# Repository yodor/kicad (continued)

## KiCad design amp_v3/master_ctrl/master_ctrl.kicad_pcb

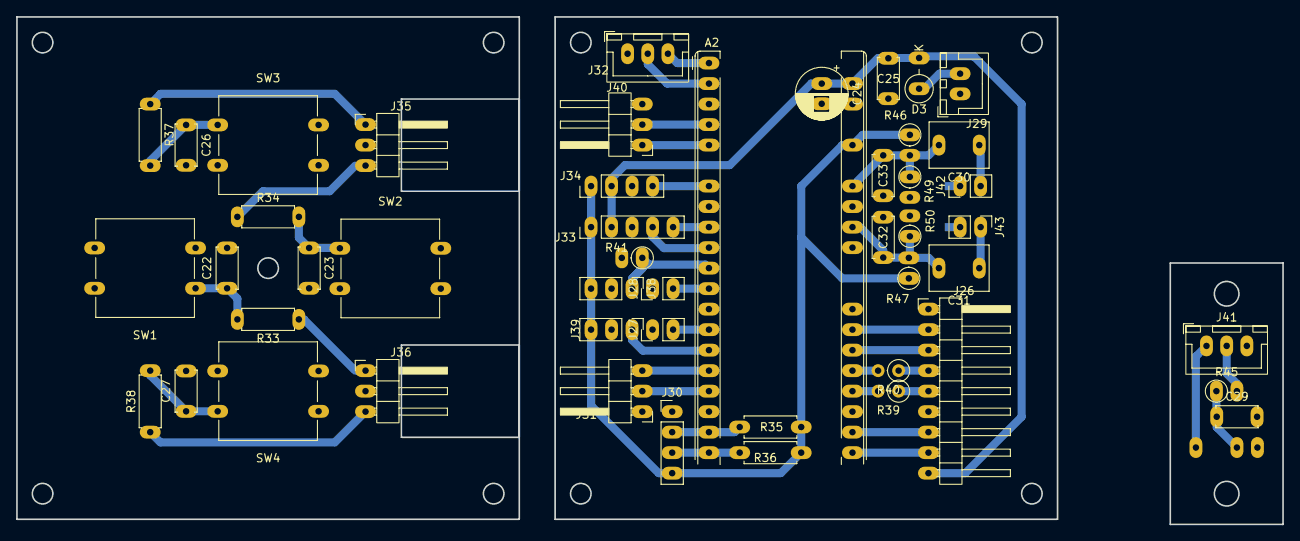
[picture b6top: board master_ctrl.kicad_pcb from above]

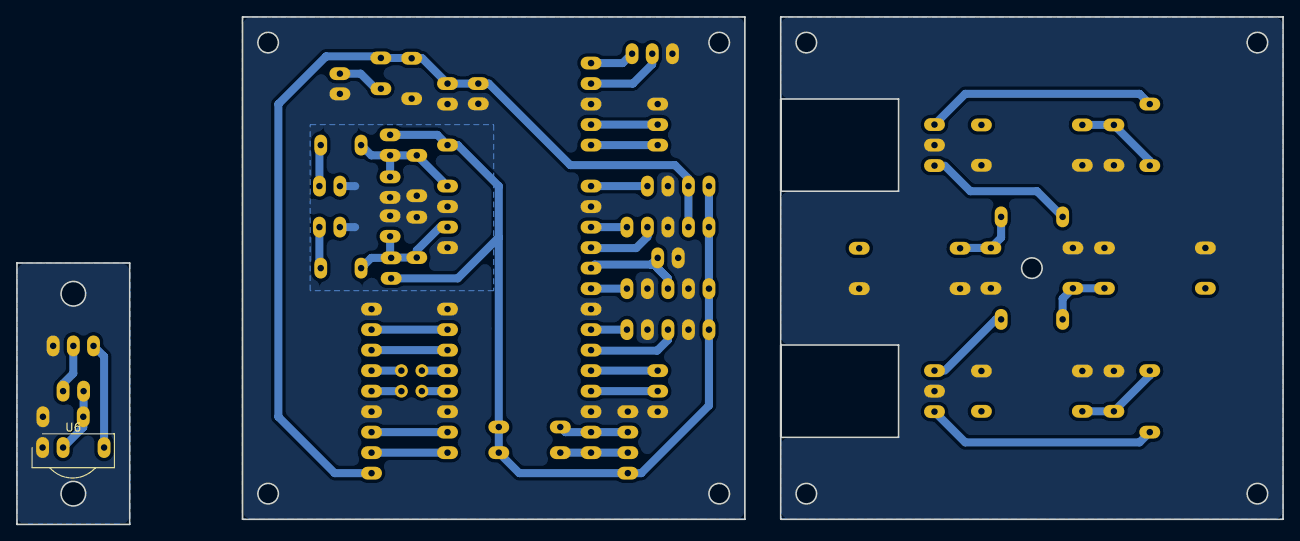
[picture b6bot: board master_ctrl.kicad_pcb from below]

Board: 2 copper layers, 156.8 x 62.9 mm, 51 parts (3 on the bottom side), 39 nets.

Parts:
A2: RaspberryPi_Pico_W; RaspberryPi_Pico_Common_THT
C22, C23, C25, C26, C27, C29: 100nF; C_Disc_D5.0mm_W2.5mm_P5.00mm
C24: 100uF low; CP_Radial_D6.3mm_P2.50mm
C30, C31: 1uF; C_Rect_L7.2mm_W5.5mm_P5.00mm_FKS2_FKP2_MKS2_MKP2
C32, C33: 10nF; C_Disc_D5.0mm_W2.5mm_P5.00mm
D3: 1n5819; D_DO-41_SOD81_P3.81mm_Vertical_CathodeUp
J26: TFT; PinHeader_1x09_P2.54mm_Horizontal
J27: PWR_CTRL; PinHeader_1x02_P2.54mm_Vertical
J28: PWR_BTN_LED; PinHeader_1x02_P2.54mm_Vertical
J29: PWR_IN; JST_XH_B2B-XH-A_1x02_P2.50mm_Vertical
J30: I2C; PinHeader_1x04_P2.54mm_Vertical
J31: BTN_VOL; PinHeader_1x03_P2.54mm_Horizontal
J32: BTN_MENU; PinHeader_1x03_P2.54mm_Horizontal
J33: ALPS; PinHeader_1x05_P2.54mm_Vertical
J34: PWR_RLY; PinHeader_1x04_P2.54mm_Vertical
J35: BTN_EXT1; PinHeader_1x03_P2.54mm_Horizontal
J36: BTN_EXT2; PinHeader_1x03_P2.54mm_Horizontal
J38: MUTE; PinHeader_1x03_P2.54mm_Vertical
J39: IR; PinHeader_1x03_P2.54mm_Vertical
J40: UART; JST_XH_B3B-XH-A_1x03_P2.50mm_Vertical
J41: IR_SENSOR; JST_XH_B3B-XH-A_1x03_P2.50mm_Vertical
J42: S_AIN_L; PinHeader_1x02_P2.54mm_Vertical
J43: S_AIN_R; PinHeader_1x02_P2.54mm_Vertical
NT3, NT4: NetTie_2; NetTie-2_SMD_Pad1.0o
R33, R34, R37, R38: 1k; R_Axial_DIN0207_L6.3mm_D2.5mm_P7.62mm_Horizontal
R35, R36: 4.7K; R_Axial_DIN0207_L6.3mm_D2.5mm_P7.62mm_Horizontal
R39, R40: 22; R_Axial_DIN0207_L6.3mm_D2.5mm_P2.54mm_Vertical
R41, R46, R47, R49, R50: 10K; R_Axial_DIN0207_L6.3mm_D2.5mm_P2.54mm_Vertical
R45: 100; R_Axial_DIN0207_L6.3mm_D2.5mm_P2.54mm_Vertical
SW1: SW_LT; SW_SPST_Omron_B3F-50xx
SW2: SW_RT; SW_SPST_Omron_B3F-50xx
SW3: SW_UP; SW_SPST_Omron_B3F-50xx
SW4: SW_DN; SW_SPST_Omron_B3F-50xx
U6: TSOP312xx; Vishay_CAST-3Pin

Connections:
/Main Board/3.3V_PICO: A2.36 (3V3), J30.4, J33.1, J34.1, J38.3, J39.3, J41.2, R35.1, R36.1, R45.2, R46.1, R47.1
/Main Board/5V_board1: D3.2 (A), J29.2
/Main Board/5v_local: A2.39 (VSYS), C24.1, C25.1, D3.1 (K), J26.9, J33.2, J34.2
/Main Board/ADC_L: A2.34 (GPIO28_ADC2), C30.2, C33.1, R46.2, R49.1
/Main Board/ADC_R: A2.32 (GPIO27_ADC1), C31.2, C32.2, R47.2, R50.1
/Main Board/AGND_L: J42.1, NT4.1
/Main Board/AGND_PICO: A2.31 (GPIO26_ADC0), A2.33 (AGND), C32.1, C33.2, NT3.2, NT4.2, R49.2, R50.2
/Main Board/AGND_R: J43.2, NT3.1
/Main Board/ALPS_L: A2.10 (GPIO7), J33.4
/Main Board/ALPS_R: A2.9 (GPIO6), J33.5
/Main Board/AUDIO_L: C30.1, J42.2
/Main Board/AUDIO_R: C31.1, J43.1
/Main Board/BTN_DN: A2.17 (GPIO13), J31.2, J36.3, R38.1
/Main Board/BTN_LT: A2.16 (GPIO12), J31.3, J36.1, R33.1
/Main Board/BTN_RT: A2.5 (GPIO3), J32.1, J35.3, R34.1
/Main Board/BTN_UP: A2.4 (GPIO2), J32.2, J35.1, R37.1
/Main Board/IR: A2.15 (GPIO11), J39.1, J41.1, U6.3 (OUT)
/Main Board/MUTE_CTRL: A2.11 (GPIO8), J38.1, R41.1
/Main Board/PWR_BTN_LED: A2.12 (GPIO9), J28.2
/Main Board/PWR_CTRL: A2.14 (GPIO10), J27.2
/Main Board/RLCTRL: A2.7 (GPIO5), J34.4
/Main Board/SCL: A2.20 (GPIO15), J30.3, R36.2
/Main Board/SDA: A2.19 (GPIO14), J30.2, R35.2
/Main Board/TFT_BLK: A2.27 (GPIO21), J26.2
/Main Board/TFT_CS: A2.22 (GPIO17), J26.7
/Main Board/TFT_DC: A2.21 (GPIO16), J26.8
/Main Board/TFT_RST: A2.26 (GPIO20), J26.3
/Main Board/TFT_SCL: J26.5, R39.1
/Main Board/TFT_SDA: J26.4, R40.1
/Main Board/UART_RX: A2.2 (GPIO1), J40.2
/Main Board/UART_TX: A2.1 (GPIO0), J40.3
GNDD: A2.3 (GND), A2.8 (GND), A2.13 (GND), A2.18 (GND), A2.23 (GND), A2.28 (GND), A2.38 (GND), C22.2, C23.2, C24.2, C25.2, C26.2, C27.2, C29.2, J26.1, J26.6, J27.1, J28.1, J29.1, J30.1, J31.1, J32.3, J33.3, J34.3, J35.2, J36.2, J38.2, J39.2, J40.1, J41.3, R41.2, SW1.2, SW2.2, SW3.2, SW4.2, U6.1 (GND)
unnamed: A2.24 (GPIO18), R39.2
unnamed: A2.25 (GPIO19), R40.2
unnamed: C22.1, R33.2, SW1.1
unnamed: C23.1, R34.2, SW2.1
unnamed: C26.1, R37.2, SW3.1
unnamed: C27.1, R38.2, SW4.1
unnamed: C29.1, R45.1, U6.2 (Vs)

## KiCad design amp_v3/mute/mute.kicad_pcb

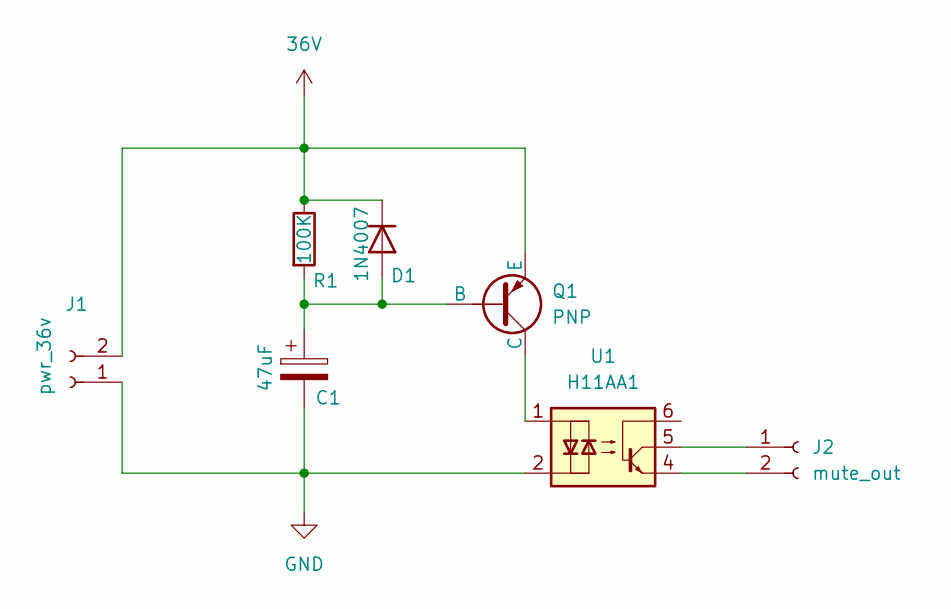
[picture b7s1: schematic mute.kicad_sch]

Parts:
C1: 47uF; CP_Radial_D6.3mm_P2.50mm
D1: 1N4007; D_DO-41_SOD81_P10.16mm_Horizontal
J1: pwr_36v; JST_XH_B2B-XH-A_1x02_P2.50mm_Vertical
J2: mute_out; JST_XH_B2B-XH-A_1x02_P2.50mm_Vertical
Q1: PNP; TO-92_Inline_Wide
R1: 100K; R_Axial_DIN0207_L6.3mm_D2.5mm_P10.16mm_Horizontal
U1: H11AA1; DIP-6_W7.62mm_Socket_LongPads

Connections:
36V: D1.1 (K), J1.2, Q1.3 (E), R1.1
GND: C1.2, J1.1, U1.2
unnamed: C1.1, D1.2 (A), Q1.2 (B), R1.2
unnamed: J2.1, U1.5
unnamed: J2.2, U1.4
unnamed: Q1.1 (C), U1.1

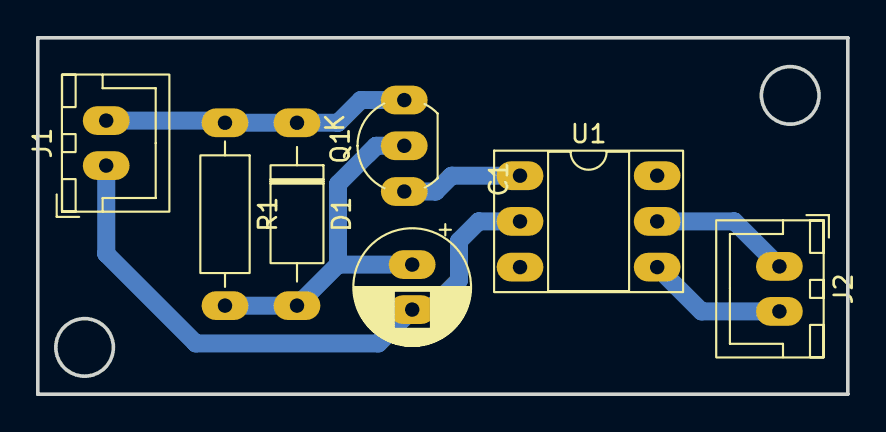
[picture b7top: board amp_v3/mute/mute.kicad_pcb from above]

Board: 2 copper layers, 45.0 x 19.8 mm, 7 parts (0 on the bottom side), 6 nets.

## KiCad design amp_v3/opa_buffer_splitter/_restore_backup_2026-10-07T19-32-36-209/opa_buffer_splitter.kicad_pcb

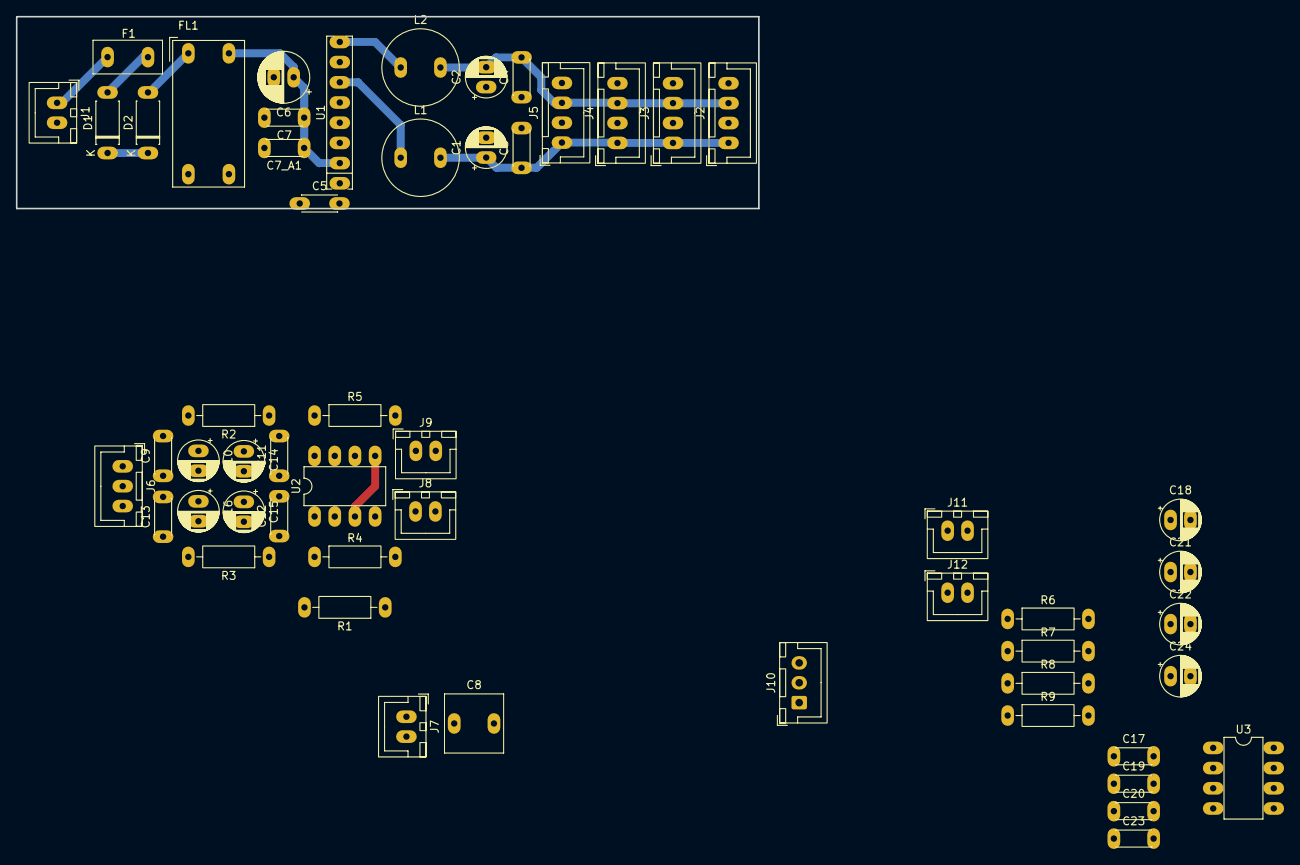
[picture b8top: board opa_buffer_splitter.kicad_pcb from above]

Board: 2 copper layers, 93.3 x 24.1 mm, 55 parts (0 on the bottom side), 32 nets.

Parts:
C1, C2, C14, C15, C21, C22: 10uF esr; CP_Radial_D5.0mm_P2.50mm
C3, C4: 1uF x7r; C_Disc_D4.3mm_W1.9mm_P5.00mm
C5: 2.2 nF, 2000 V, Y5P; C_Disc_D4.3mm_W1.9mm_P5.00mm
C6: 47uF; CP_Radial_D6.3mm_P2.50mm
C7, C7_A1: 1uF X7R; C_Disc_D4.3mm_W1.9mm_P5.00mm
C8: 2.2uF (Film or PP); C_Rect_L7.2mm_W7.2mm_P5.00mm_FKS2_FKP2_MKS2_MKP2
C9, C11, C12, C13, C17, C19, C20, C23: 100nF; C_Disc_D4.3mm_W1.9mm_P5.00mm
C10, C16, C18, C24: 4.7uF; CP_Radial_D5.0mm_P2.50mm
D1: 1N4007; D_DO-41_SOD81_P7.62mm_Horizontal
D2: 1N5338B; D_DO-41_SOD81_P7.62mm_Horizontal
F1: 1A; Fuse_Littelfuse_395Series
FL1: RN202-0.3-02-12M; Choke_Schaffner_RN202-04-8.8x18.2mm
J1: UHP_PWR; JST_XH_B2B-XH-A_1x02_P2.50mm_Vertical
J2, J3, J4, J5: OP_PWR_OUT; JST_XH_B4B-XH-A_1x04_P2.50mm_Vertical
J6, J10: OP_PWR; JST_XH_B3B-XH-A_1x03_P2.50mm_Vertical
J7, J11: AUDIO_IN; JST_XH_B2B-XH-A_1x02_P2.50mm_Vertical
J8: AOUT_MASTER; JST_XH_B2B-XH-A_1x02_P2.50mm_Vertical
J9: AOUT_VIS; JST_XH_B2B-XH-A_1x02_P2.50mm_Vertical
J12: AUDIO_OUT; JST_XH_B2B-XH-A_1x02_P2.50mm_Vertical
L1, L2: 10uH; L_Radial_D9.5mm_P5.00mm_Fastron_07HVP
R1: 100K; R_Axial_DIN0207_L6.3mm_D2.5mm_P10.16mm_Horizontal
R2, R3, R7, R8: 10R; R_Axial_DIN0207_L6.3mm_D2.5mm_P10.16mm_Horizontal
R4, R5, R9: 47R; R_Axial_DIN0207_L6.3mm_D2.5mm_P10.16mm_Horizontal
R6: 1M; R_Axial_DIN0207_L6.3mm_D2.5mm_P10.16mm_Horizontal
U1: DPB09B-12; SIP-8_19x3mm_P2.54mm
U2, U3: OPA1656; SMDIP-8_W7.62mm

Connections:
/Buffer/+12VA: C17.2, C18.1, J10.1, R7.2
/Buffer/-12VA: C23.1, C24.2, J10.3, R8.2
/Buffer/AUDIO_GND: C17.1, C18.2, C19.1, C20.2, C21.2, C22.1, C23.2, C24.1, J10.2, J11.2, J12.2, R6.1, U3.5 (+)
/Buffer/AUDIO_IN_VACTROL: J11.1, R6.2, U3.3 (+)
/Buffer/AUDIO_OUT_AMP: J12.1, R9.2
/PSU/30V_PRE: C6.1, C7.1, C7_A1.1, FL1.2, U1.2
/PSU/+12VA: C1.1, C3.1, J2.1, J3.1, J4.1, J5.1, L1.2
/PSU/+12V_DC: L1.1, U1.6
/PSU/+36V_UHP: F1.1, J1.1
/PSU/-12VA: C2.2, C4.2, J2.3, J3.3, J4.3, J5.3, L2.2
/PSU/-12V_DC: L2.1, U1.8
/PSU/AUDIO_GND: C1.2, C2.1, C3.2, C4.1, C5.2, J2.2, J2.4, J3.2, J3.4, J4.2, J4.4, J5.2, J5.4, U1.7
/PSU/GND_PRE: C5.1, C6.2, C7.2, C7_A1.2, FL1.4, U1.1
/PSU/GND_UHP: FL1.3, J1.2
/Splitter/+12VA: C9.2, C10.1, J6.1, R2.2
/Splitter/-12VA: C13.1, C16.2, J6.3, R3.2
/Splitter/AUDIO_GND: C9.1, C10.2, C11.1, C12.2, C13.2, C14.2, C15.1, C16.1, J6.2, J7.2, J8.2, J9.2, R1.2
/Splitter/AUDIO_IN: C8.2, R1.1, U2.3 (+), U2.5 (+)
/Splitter/AUDIO_OUT_MASTER: J9.1, R5.2
/Splitter/AUDIO_OUT_VACTROL: J8.1, R4.2
/Splitter/RCA_IN: C8.1, J7.1
unnamed: D1.2 (A), F1.2
unnamed: D1.1 (K), D2.1 (K)
unnamed: D2.2 (A), FL1.1
unnamed: R4.1, U2.1, U2.2 (-)
unnamed: R5.1, U2.6 (-), U2.7
unnamed: C11.2, C14.1, R2.1, U2.8 (V+)
unnamed: C12.1, C15.2, R3.1, U2.4 (V-)
unnamed: R9.1, U3.1, U3.2 (-)
unnamed: U3.6 (-), U3.7
unnamed: C19.2, C21.1, R7.1, U3.8 (V+)
unnamed: C20.1, C22.2, R8.1, U3.4 (V-)
